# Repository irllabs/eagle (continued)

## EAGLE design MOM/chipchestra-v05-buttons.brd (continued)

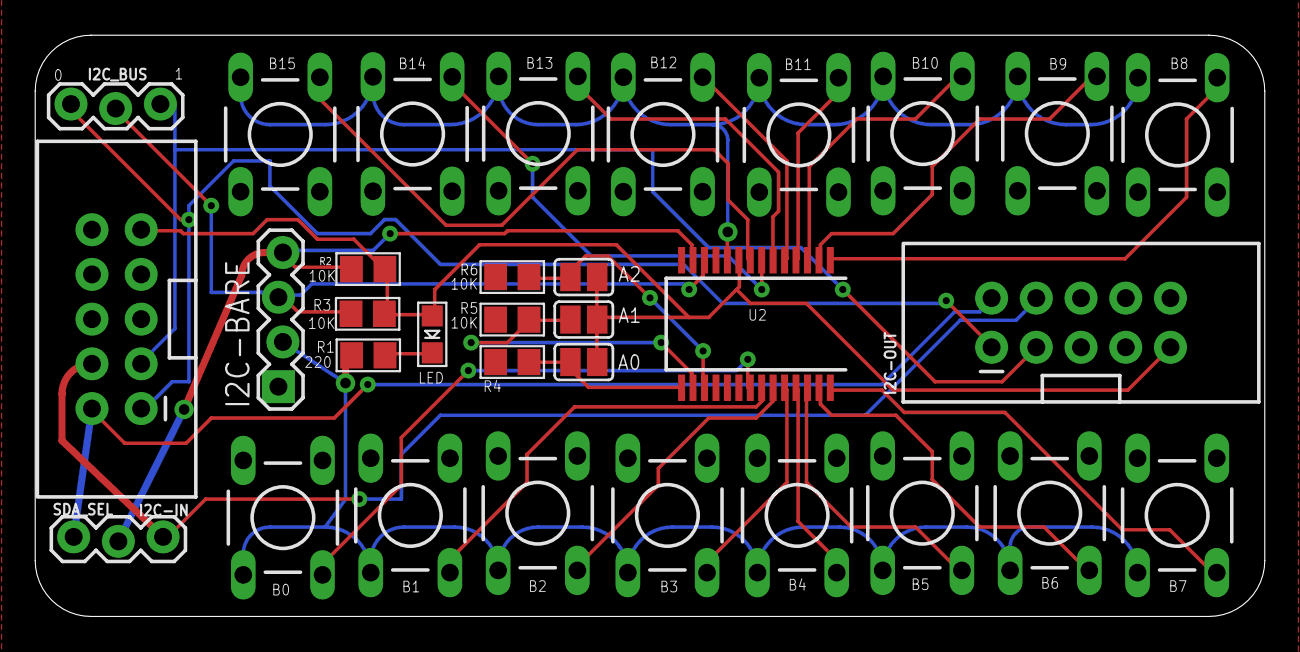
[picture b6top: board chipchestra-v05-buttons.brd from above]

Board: 2 copper layers, 69.8 x 33.0 mm, 32 parts (0 on the bottom side), 28 nets.
